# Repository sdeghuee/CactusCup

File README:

Personal project to create a set of programmable LED lights to be used for entertainment. V1 doesnt have a functioning battery charger

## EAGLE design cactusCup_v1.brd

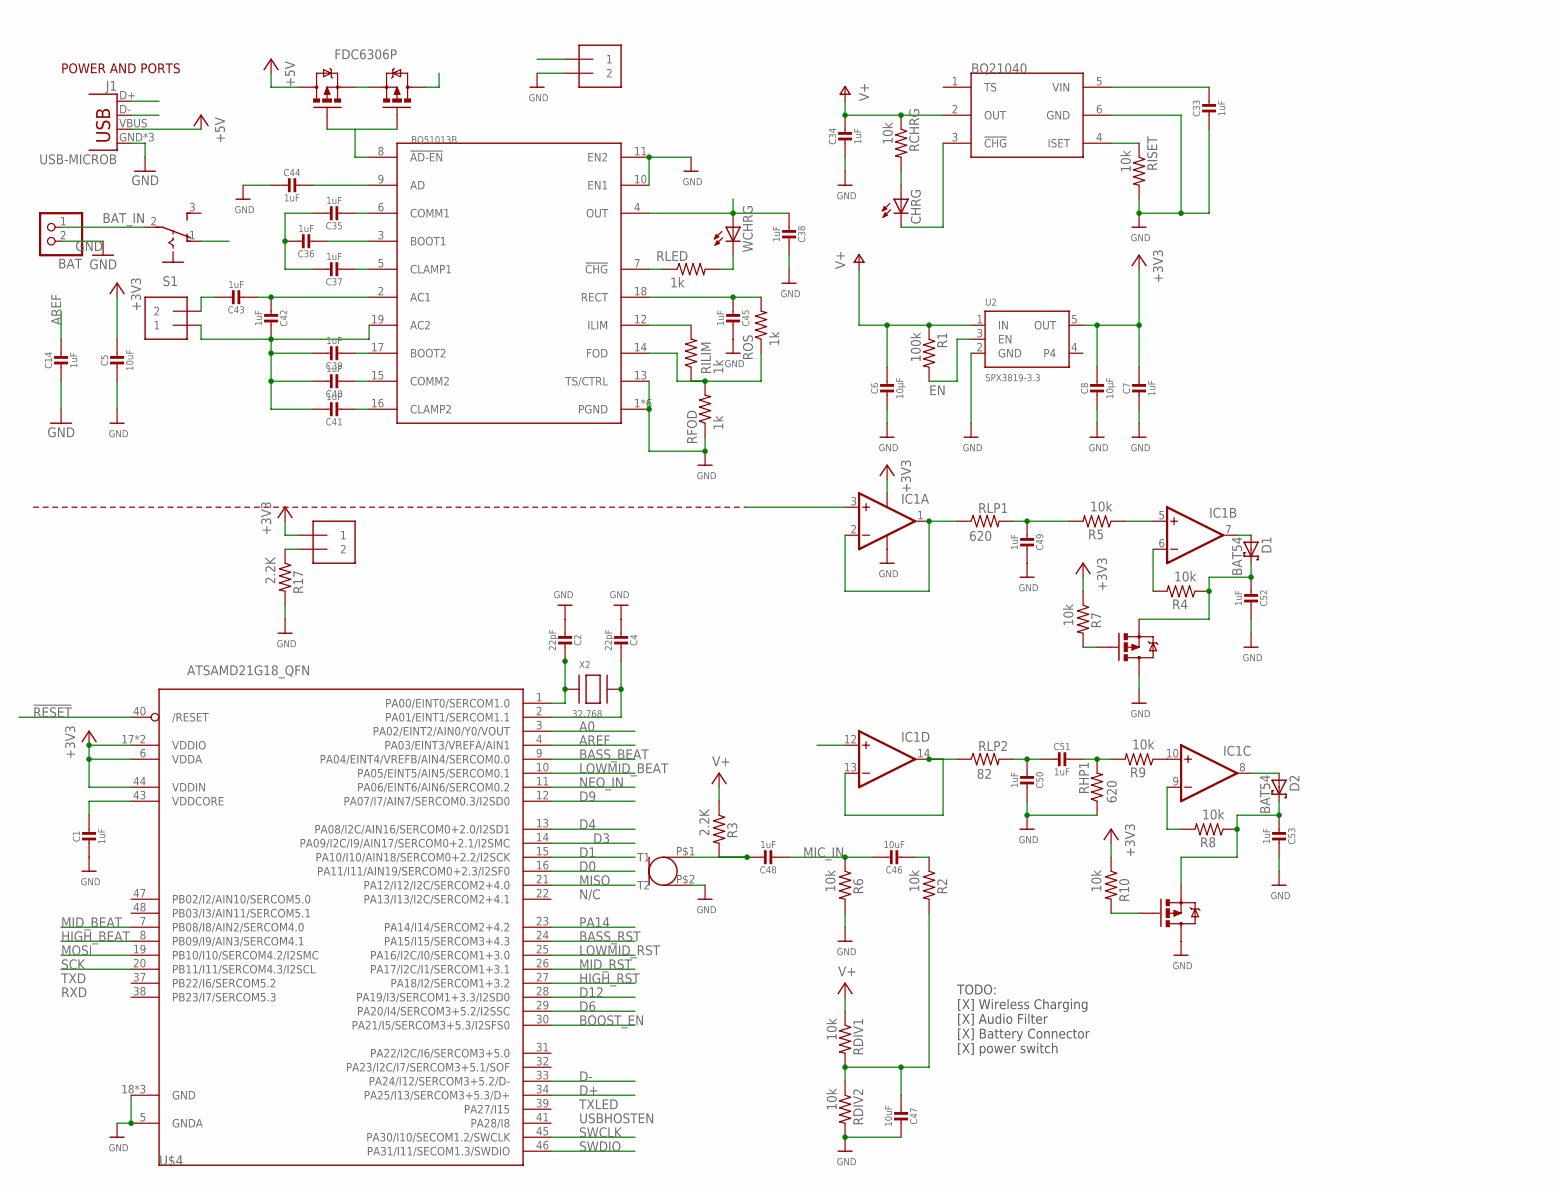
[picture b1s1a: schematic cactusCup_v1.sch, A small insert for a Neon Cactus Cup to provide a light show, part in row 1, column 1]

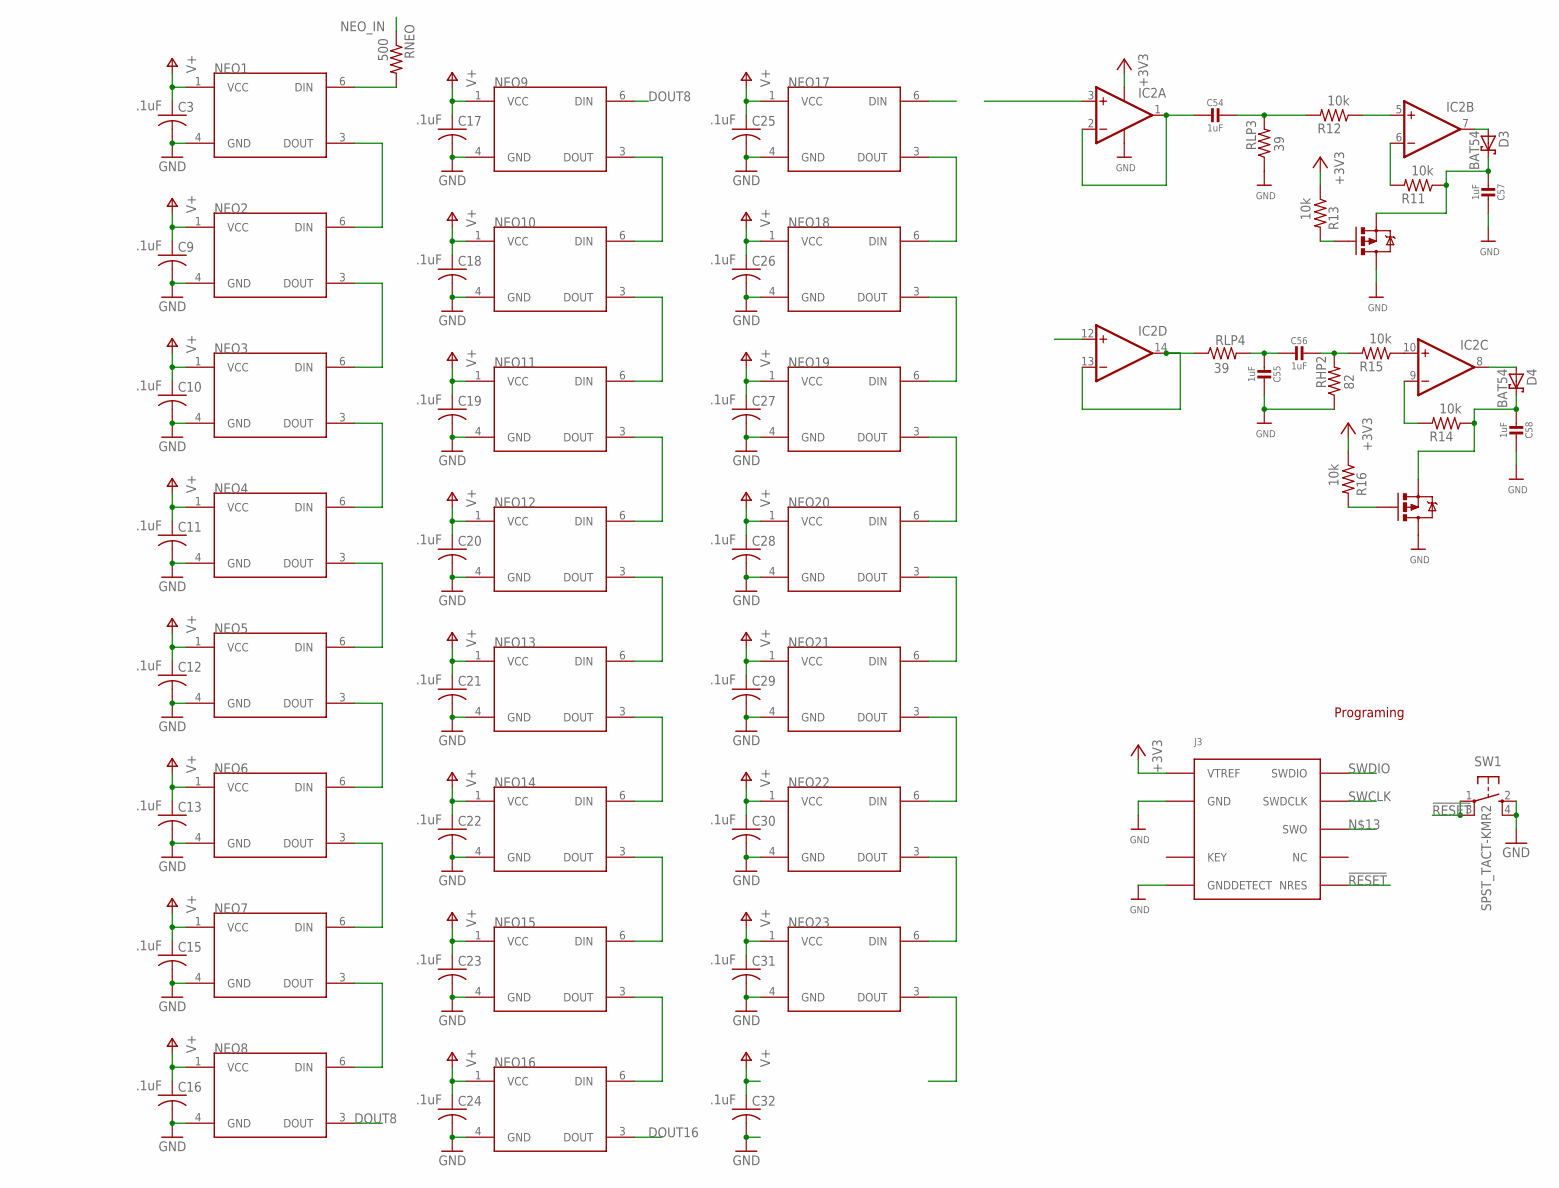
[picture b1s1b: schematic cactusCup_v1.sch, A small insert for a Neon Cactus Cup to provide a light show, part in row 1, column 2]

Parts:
BAT: JST_2PIN-SMT-RA; JST-PH-2-SMT-RA
BQ21040: BQ21040; SOT23-6
BQ51013B: BQ51013B; R-PQFP-N20
C1, C7, C14, C33, C34, C35, C36, C37, C38, C39, C40, C41, C42, C43, C44, C45, C48, C49, C50, C51, C52, C53, C54, C55, C56, C57, C58: 1uF; 0603-NO
C2, C4: 22pF; 0603-NO
C3, C9, C10, C11, C12, C13, C15, C16, C17, C18, C19, C20, C21, C22, C23, C24, C25, C26, C27, C28, C29, C30, C31, C32: .1uF; C0603
C5: 10uF; 0805-NO
C6, C8: 10µF; 0805-NO
C46, C47: 10uF; 0603-NO
CHRG: LEDCHIPLED_0603; CHIPLED_0603
COIL: 1X2-3.5MM
D1, D2, D3, D4: BAT54; SOT23
IC1, IC2: QUAD_OPAMPTS; TSSOP14
J1: USB-MICROB
J2, J4: 1X2-3.5MM
J3: JLINK_10PIN; FTSH-105-01-F-DH
NEO1, NEO2, NEO3, NEO4, NEO5, NEO6, NEO7, NEO8, NEO9, NEO10, NEO11, NEO12, NEO13, NEO14, NEO15, NEO16, NEO17, NEO18, NEO19, NEO20, NEO21, NEO22, NEO23: NEOPIXEL; RGBLED5050
R1: 100k; R0603
R2, R4, R5, R6, R7, R8, R9, R10, R11, R12, R13, R14, R15, R16: 10k; 0603-RES
R3, R17: 2.2K; 0603-RES
RCHRG: 10k; 0603-RES
RDIV1, RDIV2: 10k; 0603-RES
RFOD: 1k; 0603-RES
RHP1: 620; 0603-RES
RHP2: 82; 0603-RES
RILIM: 1k; 0603-RES
RISET: 10k; 0603-RES
RLED: 1k; 0603-RES
RLP1: 620; 0603-RES
RLP2: 82; 0603-RES
RLP3, RLP4: 39; 0603-RES
RNEO: 500; 0603-RES
ROS: 1k; 0603-RES
S1: 255SB
SW1: SPST_TACT-KMR2; KMR2
U2: SPX3819-3.3; SOT23-5
U$3, U$25, U$37: FDC6306P; SOT-23_6
U$4: ATSAMD21G18_QFN; TQFP48
U$19: CMA-4544PF-W; CMA_MIC
WCHRG: LEDCHIPLED_0603; CHIPLED_0603
X2: 32.768; XTAL3215

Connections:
!AD-EN: BQ51013B.8 (!AD-EN), U$3.1 (G), U$3.3 (G)
!RESET: J3.10 (NRES), SW1.1, SW1.3 (P1), U$4.40 (/RESET)
+1V5: C47.2, R2.2, RDIV1.2, RDIV2.1
+3V3: C5.1, C7.1, C8.1, IC1.4 (V+), IC2.4 (V+), J2.1, J3.1 (VTREF), R3.1, R7.1, R10.1, R13.1, R16.1, RDIV1.1, U2.5 (OUT), U$4.6 (VDDA), U$4.17 (VDDIO), U$4.36 (VDDIO), U$4.44 (VDDIN)
A0: U$4.3 (PA02/EINT2/AIN0/Y0/VOUT)
AREF: C14.1, U$4.4 (PA03/EINT3/VREFA/AIN1)
AUDIO_IN: C46.2, IC1.3 (+IN), IC1.12 (+IN), IC2.3 (+IN), IC2.12 (+IN), R2.1
BASS_BEAT: C52.2, D1.3 (C), R4.1, U$4.9 (PA04/EINT4/VREFB/AIN4/SERCOM0.0), U$25.5 (S)
BASS_RST: R7.2, U$4.24 (PA15/I15/SERCOM3+4.3), U$25.1 (G)
BAT_IN: BAT.1 (2), S1.2
BOOST_EN: U$4.30 (PA21/I5/SERCOM3+5.3/I2SFS0)
D0: U$4.16 (PA11/I11/AIN19/SERCOM0+2.3/I2SF0)
D1: U$4.15 (PA10/I10/AIN18/SERCOM0+2.2/I2SCK)
D3: U$4.14 (PA09/I2C/I9/AIN17/SERCOM0+2.1/I2SMC)
D4: U$4.13 (PA08/I2C/AIN16/SERCOM0+2.0/I2SD1)
D6: J2.2, R17.1, U$4.29 (PA20/I4/SERCOM3+5.2/I2SSC)
D9: U$4.12 (PA07/I7/AIN7/SERCOM0.3/I2SD0)
D12: U$4.28 (PA19/I3/SERCOM1+3.3/I2SD0)
D+: J1.D+, U$4.34 (PA25/I13/SERCOM3+5.3/D+)
D-: J1.D-, U$4.33 (PA24/I12/SERCOM3+5.2/D-)
DOUT8: NEO8.3 (DOUT), NEO9.6 (DIN)
DOUT16: NEO16.3 (DOUT), NEO17.6 (DIN)
EN: R1.2, U2.3 (EN)
GND: BAT.2 (1), BQ21040.6 (GND), BQ51013B.1 (PGND), BQ51013B.10 (EN1), BQ51013B.11 (EN2), BQ51013B.13 (TS/CTRL), BQ51013B.20 (PGND), BQ51013B.E@1 (PGND), BQ51013B.E@2 (PGND), BQ51013B.E@3 (PGND), BQ51013B.E@4 (PGND), C1.2, C2.2, C3.2, C4.2, C5.2, C6.2, C7.2, C8.2, C9.2, C10.2, C11.2, C12.2, C13.2, C14.2, C15.2, C16.2, C17.2, C18.2, C19.2, C20.2, C21.2, C22.2, C23.2, C24.2, C25.2, C26.2, C27.2, C28.2, C29.2, C30.2, C31.2, C32.2, C33.2, C34.2, C38.1, C44.2, C45.1, C47.1, C49.1, C50.1, C52.1, C53.1, C55.1, C57.1, C58.1, IC1.11 (V-), IC2.11 (V-), J1.GND, J1.MT1 (GND), J1.MT2 (GND), J3.3 (GND), J3.5 (GND), J3.9 (GNDDETECT), J4.2, NEO1.4 (GND), NEO2.4 (GND), NEO3.4 (GND), NEO4.4 (GND), NEO5.4 (GND), NEO6.4 (GND), NEO7.4 (GND), NEO8.4 (GND), NEO9.4 (GND), NEO10.4 (GND), NEO11.4 (GND), NEO12.4 (GND), NEO13.4 (GND), NEO14.4 (GND), NEO15.4 (GND), NEO16.4 (GND), NEO17.4 (GND), NEO18.4 (GND), NEO19.4 (GND), NEO20.4 (GND), NEO21.4 (GND), NEO22.4 (GND), NEO23.4 (GND), R6.2, R17.2, RDIV2.2, RFOD.1, RHP1.1, RHP2.1, RISET.2, RLP3.1, SW1.2 (S), SW1.4 (S1), U2.2 (GND), U$4.5 (GNDA), U$4.18 (GND), U$4.35 (GND), U$4.42 (GND), U$19.P$2 (T2), U$25.4 (D), U$25.6 (D), U$37.4 (D), U$37.6 (D)
HIGH_BEAT: C57.2, D3.3 (C), R11.1, U$4.8 (PB09/I9/AIN3/SERCOM4.1), U$37.5 (S)
HIGH_RST: R13.2, U$4.27 (PA18/I2/SERCOM1+3.2), U$37.1 (G)
LOWMID_BEAT: C53.2, D2.3 (C), R8.1, U$4.10 (PA05/EINT5/AIN5/SERCOM0.1), U$25.2 (S)
LOWMID_RST: R10.2, U$4.25 (PA16/I2C/I0/SERCOM1+3.0), U$25.3 (G)
MIC_IN: C46.1, C48.2, R6.1
MID_BEAT: C58.2, D4.3 (C), R14.1, U$4.7 (PB08/I8/AIN2/SERCOM4.0), U$37.2 (S)
MID_RST: R16.2, U$4.26 (PA17/I2C/I1/SERCOM1+3.1), U$37.3 (G)
MISO: U$4.21 (PA12/I12/I2C/SERCOM2+4.0)
MOSI: U$4.19 (PB10/I10/SERCOM4.2/I2SMC)
unnamed: NEO1.3 (DOUT), NEO2.6 (DIN)
unnamed: NEO3.3 (DOUT), NEO4.6 (DIN)
unnamed: NEO2.3 (DOUT), NEO3.6 (DIN)
unnamed: NEO5.3 (DOUT), NEO6.6 (DIN)
unnamed: C2.1, U$4.1 (PA00/EINT0/SERCOM1.0), X2.P$1
unnamed: NEO7.3 (DOUT), NEO8.6 (DIN)
unnamed: C4.1, U$4.2 (PA01/EINT1/SERCOM1.1), X2.P$2
unnamed: NEO6.3 (DOUT), NEO7.6 (DIN)
unnamed: NEO4.3 (DOUT), NEO5.6 (DIN)
unnamed: NEO9.3 (DOUT), NEO10.6 (DIN)
unnamed: NEO11.3 (DOUT), NEO12.6 (DIN)
unnamed: NEO10.3 (DOUT), NEO11.6 (DIN)
unnamed: NEO13.3 (DOUT), NEO14.6 (DIN)
unnamed: NEO15.3 (DOUT), NEO16.6 (DIN)
unnamed: NEO14.3 (DOUT), NEO15.6 (DIN)
unnamed: NEO12.3 (DOUT), NEO13.6 (DIN)
unnamed: NEO17.3 (DOUT), NEO18.6 (DIN)
unnamed: NEO19.3 (DOUT), NEO20.6 (DIN)
unnamed: NEO18.3 (DOUT), NEO19.6 (DIN)
unnamed: NEO21.3 (DOUT), NEO22.6 (DIN)
unnamed: NEO22.3 (DOUT), NEO23.6 (DIN)
unnamed: NEO20.3 (DOUT), NEO21.6 (DIN)
unnamed: CHRG.A, RCHRG.2
unnamed: BQ21040.3 (!CHG), CHRG.C
unnamed: BQ21040.4 (ISET), RISET.1
unnamed: NEO1.6 (DIN), RNEO.2
unnamed: BQ51013B.6 (COMM1), C35.2
unnamed: U$3.2 (S), U$3.5 (S)
unnamed: BQ51013B.7 (!CHG), RLED.1
unnamed: C35.1, C36.1, C37.1
unnamed: BQ51013B.3 (BOOT1), C36.2
unnamed: BQ51013B.5 (CLAMP1), C37.2
unnamed: BQ51013B.2 (AC1), C42.2, C43.2
unnamed: BQ51013B.19 (AC2), C39.1, C40.1, C41.1, C42.1, COIL.1
unnamed: BQ51013B.17 (BOOT2), C39.2
unnamed: BQ51013B.16 (CLAMP2), C41.2
unnamed: BQ51013B.15 (COMM2), C40.2
unnamed: BQ51013B.18 (RECT), C45.2, ROS.2
unnamed: BQ51013B.14 (FOD), RFOD.2, RILIM.1, ROS.1
unnamed: BQ51013B.12 (ILIM), RILIM.2
unnamed: C43.1, COIL.2
unnamed: C48.1, R3.2, U$19.P$1 (T1)
unnamed: IC1.1 (OUT), IC1.2 (-IN), RLP1.1
unnamed: C49.2, R5.2, RLP1.2
unnamed: C50.2, C51.2, RLP2.2
unnamed: C51.1, R9.2, RHP1.2
unnamed: IC1.6 (-IN), R4.2
unnamed: IC1.5 (+IN), R5.1
unnamed: D1.1 (A), IC1.7 (OUT)
unnamed: C54.2, IC2.1 (OUT), IC2.2 (-IN)
unnamed: C54.1, R12.2, RLP3.2
unnamed: IC1.10 (+IN), R9.1
unnamed: D2.1 (A), IC1.8 (OUT)
unnamed: IC1.9 (-IN), R8.2
unnamed: IC1.13 (-IN), IC1.14 (OUT), RLP2.1
unnamed: C55.2, C56.2, RLP4.2
unnamed: C56.1, R15.2, RHP2.2
unnamed: IC2.6 (-IN), R11.2
unnamed: IC2.5 (+IN), R12.1
unnamed: D3.1 (A), IC2.7 (OUT)
unnamed: D4.1 (A), IC2.8 (OUT)
unnamed: IC2.10 (+IN), R15.1
unnamed: IC2.9 (-IN), R14.2
unnamed: IC2.13 (-IN), IC2.14 (OUT), RLP4.1
NEO_IN: RNEO.1, U$4.11 (PA06/EINT6/AIN6/SERCOM0.2)
PA14: U$4.23 (PA14/I14/SERCOM2+4.2)
SCK: U$4.20 (PB11/I11/SERCOM4.3/I2SCL)
SWCLK: J3.4 (SWDCLK), U$4.45 (PA30/I10/SECOM1.2/SWCLK)
SWDIO: J3.2 (SWDIO), U$4.46 (PA31/I11/SECOM1.3/SWDIO)
VBAT: BQ21040.2 (OUT), C3.1, C6.1, C9.1, C10.1, C11.1, C12.1, C13.1, C15.1, C16.1, C17.1, C18.1, C19.1, C20.1, C21.1, C22.1, C23.1, C24.1, C25.1, C26.1, C27.1, C28.1, C29.1, C30.1, C31.1, C32.1, C34.1, NEO1.1 (VCC), NEO2.1 (VCC), NEO3.1 (VCC), NEO4.1 (VCC), NEO5.1 (VCC), NEO6.1 (VCC), NEO7.1 (VCC), NEO8.1 (VCC), NEO9.1 (VCC), NEO10.1 (VCC), NEO11.1 (VCC), NEO12.1 (VCC), NEO13.1 (VCC), NEO14.1 (VCC), NEO15.1 (VCC), NEO16.1 (VCC), NEO17.1 (VCC), NEO18.1 (VCC), NEO19.1 (VCC), NEO20.1 (VCC), NEO21.1 (VCC), NEO22.1 (VCC), NEO23.1 (VCC), R1.1, RCHRG.1, S1.1 (O), U2.1 (IN)
VBUS: BQ21040.5 (VIN), BQ51013B.4 (OUT), C33.1, C38.2, J4.1, U$3.6 (D), WCHRG.A
VDDCORE: C1.1, U$4.43 (VDDCORE)
VUSB: BQ51013B.9 (AD), C44.1, J1.VBUS, U$3.4 (D)
WCHRG: RLED.2, WCHRG.C

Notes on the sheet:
POWER AND PORTS
Programing
N/C
TXLED
USBHOSTEN
TXD
RXD
TODO: [X] Wireless Charging [X] Audio Filter [X] Battery Connector [X] power switch

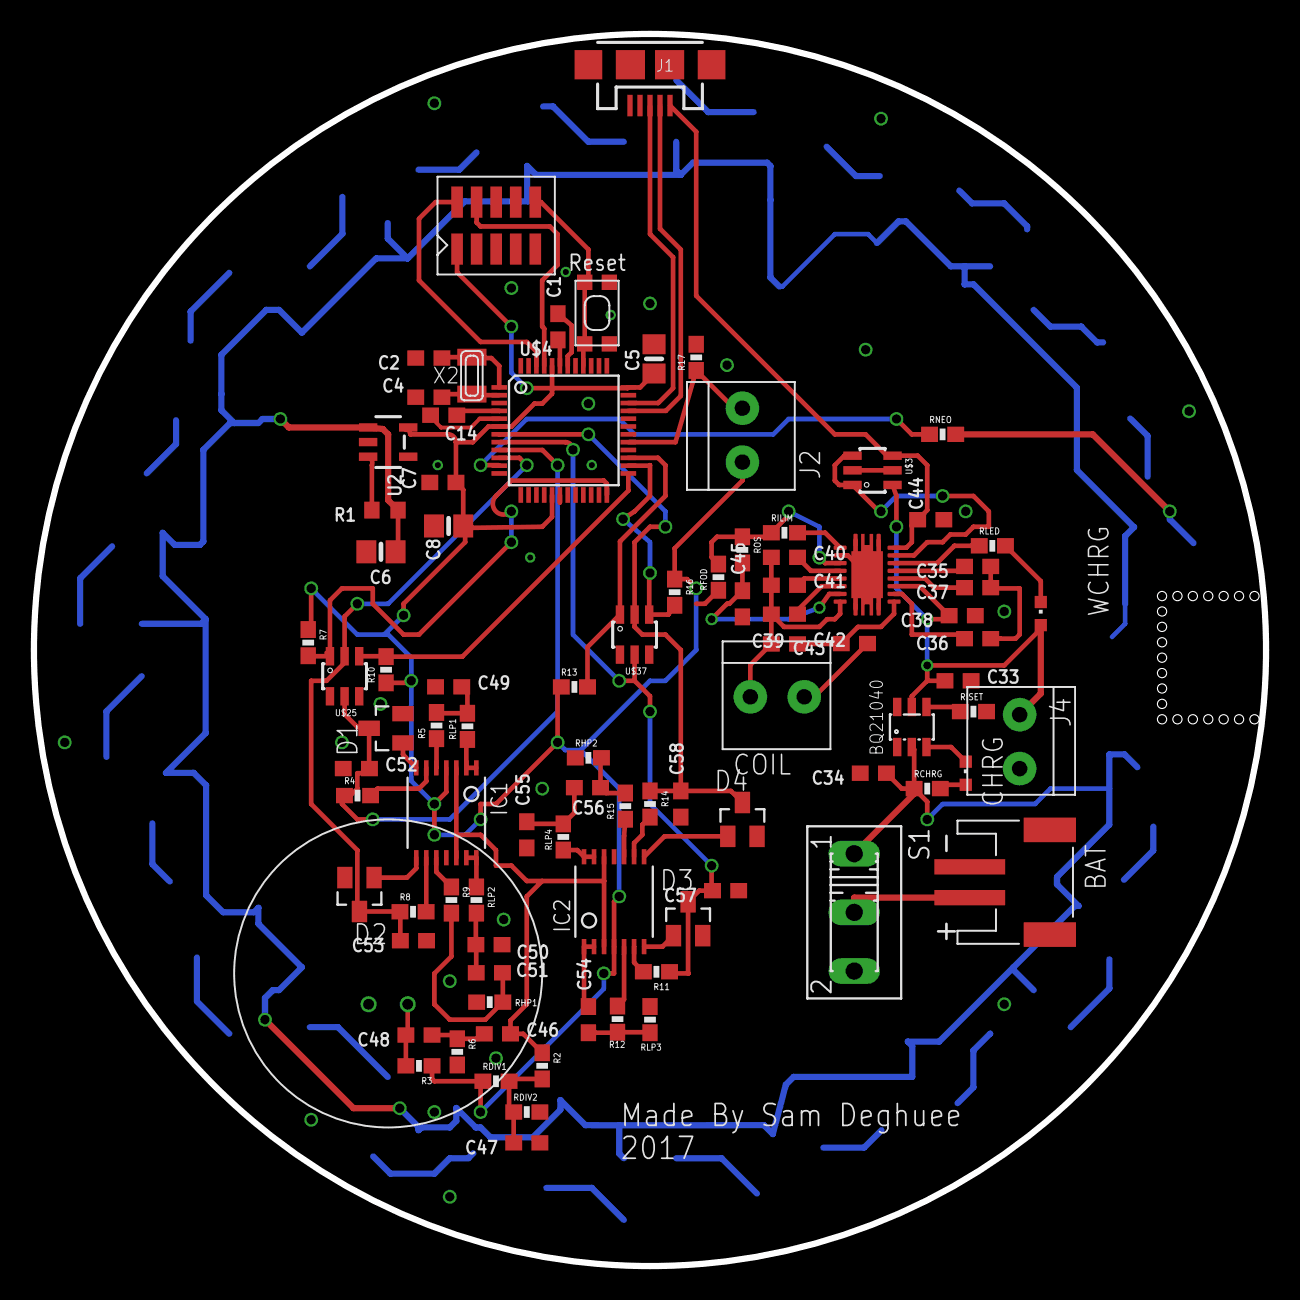
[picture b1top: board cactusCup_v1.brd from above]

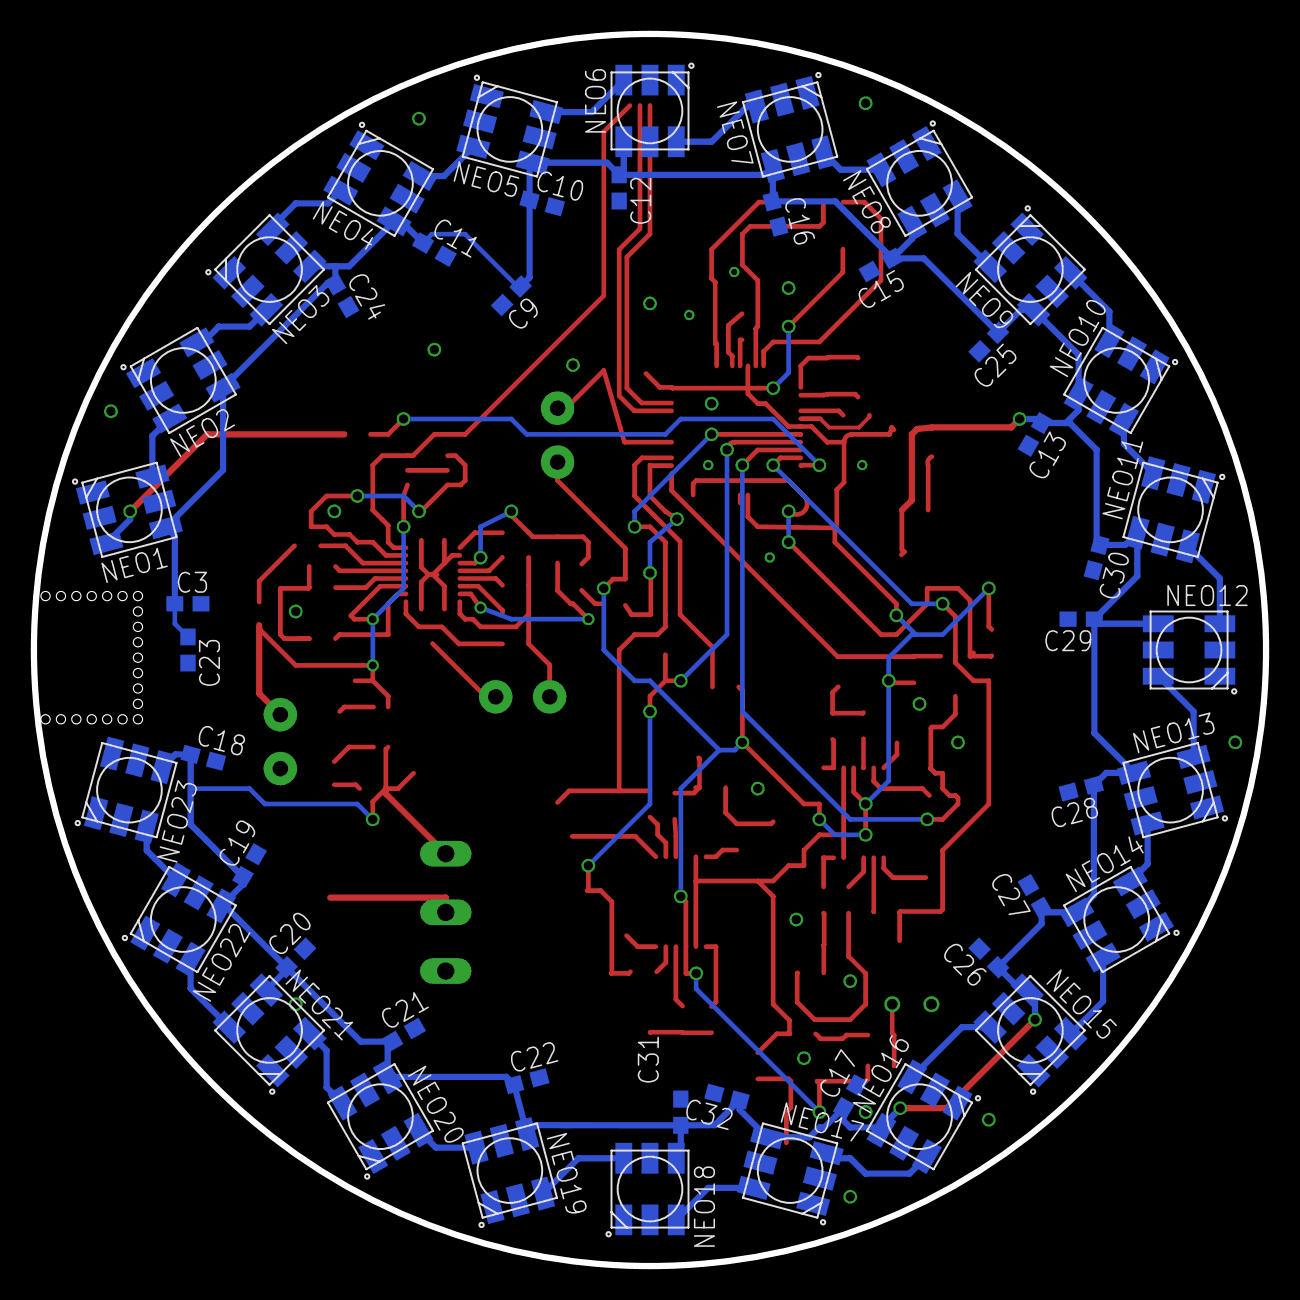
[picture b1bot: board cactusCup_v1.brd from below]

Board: 2 copper layers, 80.0 x 80.0 mm, 138 parts (47 on the bottom side), 95 nets.

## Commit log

2017-10-28 Creating Repository with files
2018-01-14 Updated code for final version of mini cactuscup
2018-02-02 Update with CAD
2018-02-03 Added label for battery circuit

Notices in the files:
parts and their libraries:
microbuilder: This work is placed in the public domain, and may be freely used for commercial and non-commercial work with the following conditions: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
SparkFun-Connectors: Licensing: Creative Commons ShareAlike 4.0 International - https://creativecommons.org/licenses/by-sa/4.0
